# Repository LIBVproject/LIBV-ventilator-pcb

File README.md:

# LIBV Open Source Ventilator

Check out our [www.bvmvent.org](https://www.bvmvent.org/) for updates.

**The Problem:** The COVID-19 Pandemic has highlighted the scarcity of potentially life-saving resources around the world.

**Our Challenge:** Design and Engineer an Open Source, low cost (sub $150) ventilator using readily available materials for rapid deployment in developing countries where there may not be an alternative.

Who we are: A Collective of Engineers, Medics and Scientists from across the world, centred around a hub in Phnom Penh, Cambodia.
Help Us: We need Volunteers, a Community of Contributors and Donors to join us and help us deliver our vision.

## Arduino Program

Check out our [Arduino Program](https://github.com/LIBVproject/LIBV-ventilator).

## Electronics PCB

The LIBV electronics are based on an Arduino Nano (Atmega328) architecture.

### Circuit Digram

### Printed PCB

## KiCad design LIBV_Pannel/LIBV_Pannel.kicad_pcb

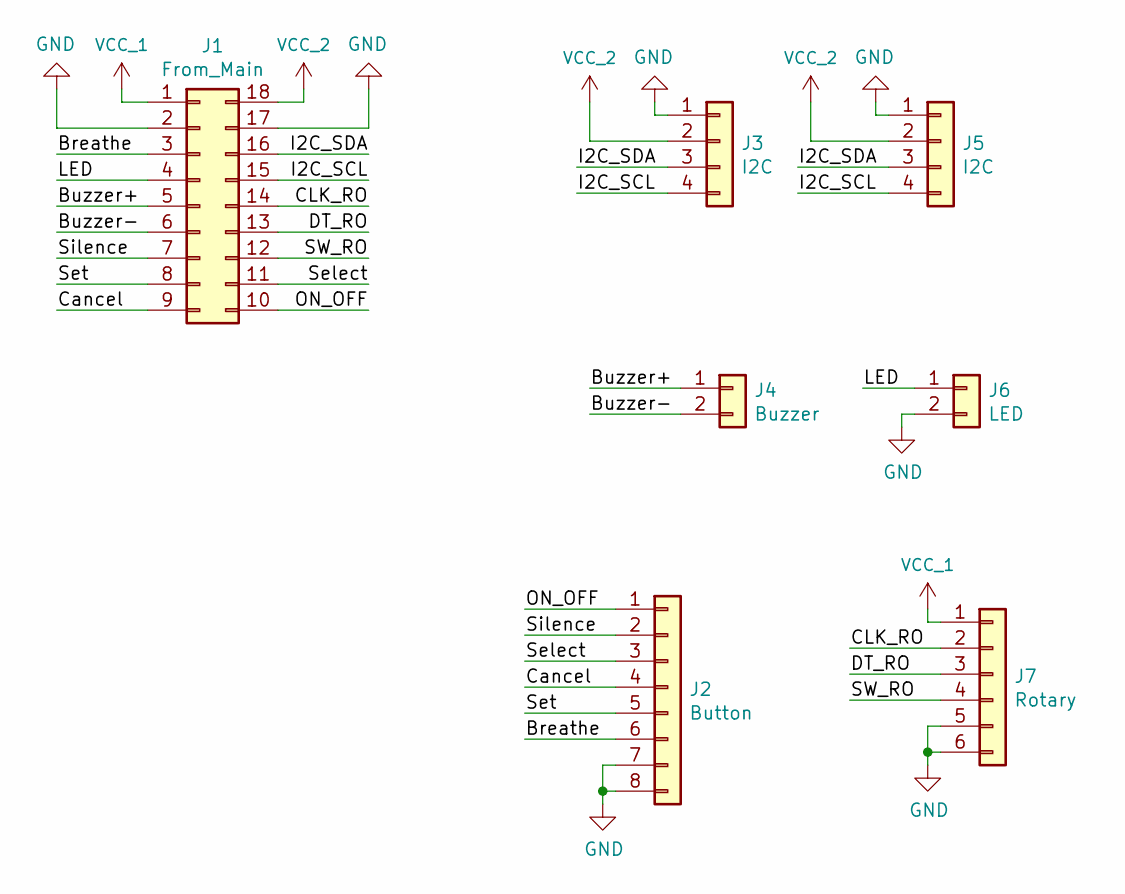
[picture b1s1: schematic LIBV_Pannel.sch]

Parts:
J1: From_Main; PinHeader_2x09_P2.54mm_Vertical
J2: Button; JST_PH_B8B-PH-K_1x08_P2.00mm_Vertical
J3, J5: I2C; JST_PH_B4B-PH-K_1x04_P2.00mm_Vertical
J4: Buzzer; JST_PH_B2B-PH-K_1x02_P2.00mm_Vertical
J6: LED; JST_PH_B2B-PH-K_1x02_P2.00mm_Vertical
J7: Rotary; JST_PH_B6B-PH-K_1x06_P2.00mm_Vertical

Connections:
/Breathe: J1.3, J2.6
/Buzzer+: J1.5, J4.1
/Buzzer-: J1.6, J4.2
/CLK_RO: J1.14, J7.2
/Cancel: J1.9, J2.4
/DT_RO: J1.13, J7.3
/I2C_SCL: J1.15, J3.4, J5.4
/I2C_SDA: J1.16, J3.3, J5.3
/LED: J1.4, J6.1
/ON_OFF: J1.10, J2.1
/SW_RO: J1.12, J7.4
/Select: J1.11, J2.3
/Set: J1.8, J2.5
/Silence: J1.7, J2.2
GND: J1.2, J1.17, J2.7, J2.8, J3.1, J5.1, J6.2, J7.5, J7.6
VCC_1: J1.1, J7.1
VCC_2: J1.18, J3.2, J5.2

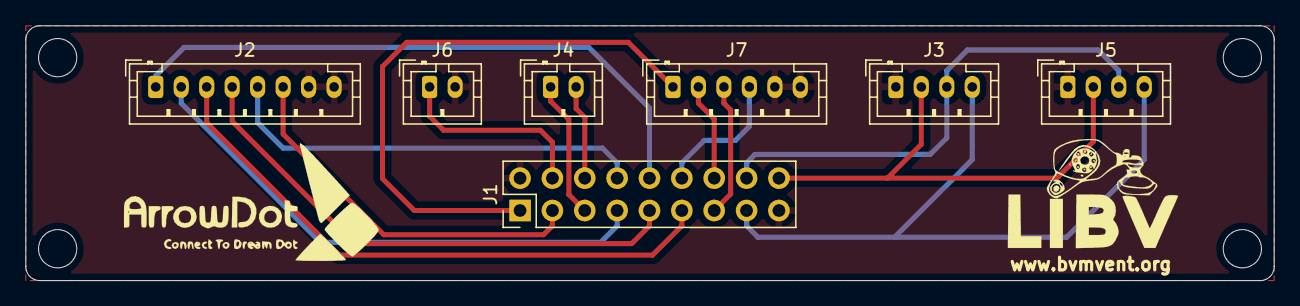
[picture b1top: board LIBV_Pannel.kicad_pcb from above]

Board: 2 copper layers, 98.0 x 20.0 mm, 7 parts (0 on the bottom side), 17 nets.

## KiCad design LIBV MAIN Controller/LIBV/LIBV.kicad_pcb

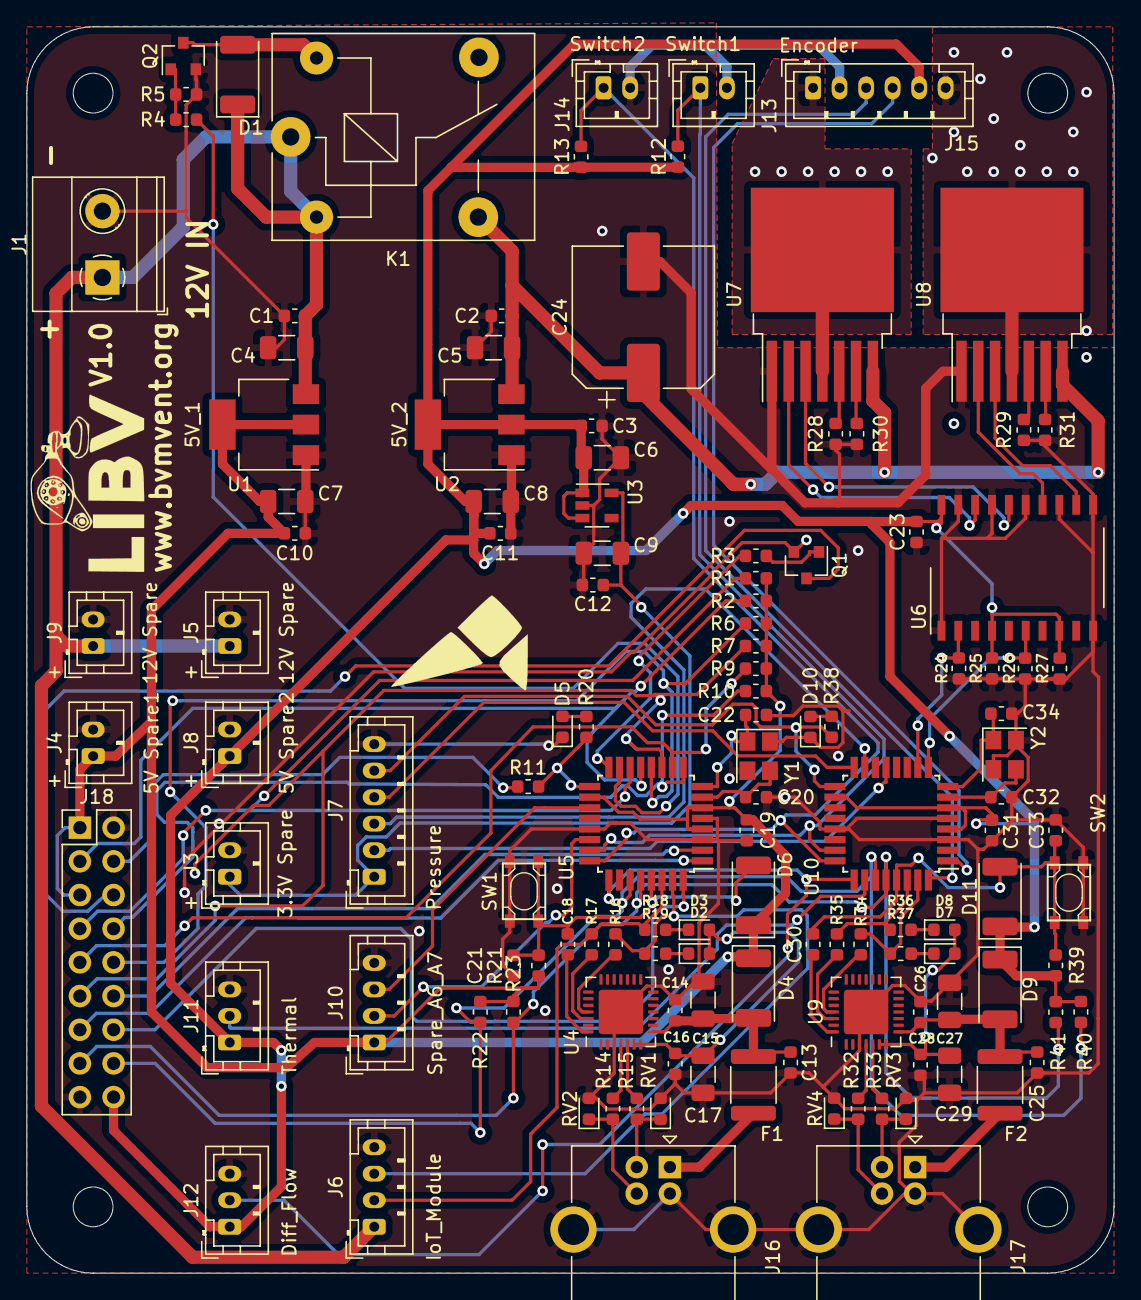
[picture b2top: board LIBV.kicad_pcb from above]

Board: 2 copper layers, 82.0 x 94.0 mm, 125 parts (0 on the bottom side), 85 nets.

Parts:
C1, C2, C3, C10, C11, C12, C13, C14, C16, C18, C19, C25, C26, C28, C30, C31: 100n; C_0603_1608Metric
C4, C5, C6, C7, C8, C9, C15, C17, C27, C29: 10u; C_1206_3216Metric
C20, C21, C22, C32, C33, C34: 22p; C_0603_1608Metric
C23: 100p; C_0603_1608Metric
C24: 470u; CP_Elec_10x10.5
D1, D6, D11: D; D_2010_5025Metric
D2, D7: TX0; LED_0603_1608Metric
D3, D8: RX0; LED_0603_1608Metric
D4, D9: SS34; D_2010_5025Metric
D5, D10: LED; LED_0603_1608Metric
F1, F2: Fuse_USB; Fuse_1812_4532Metric
J1: Power Input; TerminalBlock_Phoenix_MKDS-1,5-2_1x02_P5.00mm_Horizontal
J3: 3.3V Spare; JST_PH_B2B-PH-K_1x02_P2.00mm_Vertical
J4: 5V Spare1; JST_PH_B2B-PH-K_1x02_P2.00mm_Vertical
J5, J9: 12V Spare; JST_PH_B2B-PH-K_1x02_P2.00mm_Vertical
J6: IoT_Module; JST_PH_B4B-PH-K_1x04_P2.00mm_Vertical
J7: Pressure; JST_PH_B6B-PH-K_1x06_P2.00mm_Vertical
J8: 5V Spare2; JST_PH_B2B-PH-K_1x02_P2.00mm_Vertical
J10: Spare_A6_A7; JST_PH_B4B-PH-K_1x04_P2.00mm_Vertical
J11: Thermal; JST_PH_B3B-PH-K_1x03_P2.00mm_Vertical
J12: Diff_Flow; JST_PH_B3B-PH-K_1x03_P2.00mm_Vertical
J13: Switch1; JST_PH_B2B-PH-K_1x02_P2.00mm_Vertical
J14: Switch2; JST_PH_B2B-PH-K_1x02_P2.00mm_Vertical
J15: Encoder; JST_PH_B6B-PH-K_1x06_P2.00mm_Vertical
J16, J17: USB_B; USB_B_OST_USB-B1HSxx_Horizontal
J18: To_Pannel; PinHeader_2x09_P2.54mm_Vertical
K1: SANYOU_SRD_Form_C; Relay_SPDT_SANYOU_SRD_Series_Form_C
Q1, Q2: 1P; SOT-23
R1, R2, R5, R6, R7, R9, R10, R12, R13, R21, R22, R23, R39, R40, R41: 10k; R_0603_1608Metric
R3, R4, R11, R16, R17, R18, R19, R24, R25, R26, R27, R28, R29, R30, R31, R34, R35, R36, R37: 1k; R_0603_1608Metric
R14, R15, R32, R33: 22; R_0603_1608Metric
R20, R38: 470; R_0603_1608Metric
RV1, RV2, RV3, RV4: ESD; D_0603_1608Metric
SW1, SW2: RST; Button_Switch_3.2x4.2
U1, U2: AMS1117-5.0; SOT-223-3_TabPin2
U3: LP2985-3.3; SOT-23-5
U4, U9: CP2102N-A01-GQFN28; QFN-28-1EP_5x5mm_P0.5mm_EP3.35x3.35mm
U5, U10: ATmega328-AU; TQFP-32_7x7mm_P0.8mm
U6: 74HC244; SO-20_12.8x7.5mm_P1.27mm
U7, U8: BTN7970B; TO-263-7_TabPin8
Y1, Y2: 16Mz; Crystal_SMD_3225-4Pin_3.2x2.5mm

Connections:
+3V3: C9.1, C12.1, J3.1, J7.1, U3.5
+12V: C1.1, C4.1, D1.1, J1.1, J5.1, J6.1, J9.1, K1.1, K1.2, U1.3
/ArduinoNano1/+3.3V: C16.1, C17.1, D2.2, D3.2, U4.6, U4.7
/ArduinoNano1/Reset: C18.1, C21.1, D6.2, R21.2, SW1.1, U5.29
/ArduinoNano1/VBUS: C13.1, C14.1, C15.1, D4.2, F1.1, U4.8
/ArduinoNano1/XTAL1: C20.1, U5.7, Y1.3
/ArduinoNano1/XTAL2: C22.1, U5.8, Y1.1
/ArduinoNano2/+3.3V: C28.1, C29.1, D7.2, D8.2, U9.6, U9.7
/ArduinoNano2/RX0: R35.1, R36.1, U10.30
/ArduinoNano2/Reset: C30.1, C33.1, D11.2, R39.2, SW2.1, U10.29
/ArduinoNano2/TX0: R34.1, R37.1, U10.31
/ArduinoNano2/VBUS: C25.1, C26.1, C27.1, D9.2, F2.1, U9.8
/ArduinoNano2/XTAL1: C32.1, U10.7, Y2.3
/ArduinoNano2/XTAL2: C34.1, U10.8, Y2.1
/BTS7960/M+: J15.1, U7.4, U7.8
/BTS7960/M-: J15.6, U8.4, U8.8
/Breathe: J18.3, R2.2, U5.13
/Buzzer: R3.2, U5.16
/Buzzer-: J18.6, Q1.3
/CLK_RO: J18.14, U5.32
/Cancel: J18.9, R9.2, U5.10
/DT_RO: J18.13, U5.1
/Diff_Flow: J12.2, U5.25, U10.25
/I2C_SCL: J18.15, R23.2, R41.2, U5.28, U10.28
/I2C_SDA: J18.16, R22.2, R40.2, U5.27, U10.27
/LED: R11.2, R20.1, U5.17
/L_PWM: R24.2, U6.2, U10.10
/N1_A6: J10.3, U5.19
/N1_A7: J10.2, U5.22
/N1_RX0: J6.2, R17.1, R18.1, U5.30
/N1_TX0: J6.3, R16.1, R19.1, U5.31
/N2_D9: J7.2, U10.13
/N2_D11: J7.3, U10.15
/N2_D12: J7.4, U10.16
/N2_D13: J7.5, R38.1, U10.17
/ON_OFF: J18.10, R6.2, U5.12
/R_PWM: R26.2, U6.6, U10.9
/Relay_Pin: R4.2, U5.15
/SW_RO: J18.12, U5.2
/Select: J18.11, R7.2, U5.11
/Set: J18.8, R10.2, U5.9
/Silence: J18.7, R1.2, U5.14
/Switch1: J13.1, R12.2, U5.23, U10.23
/Switch2: J14.1, R13.2, U5.24, U10.24
/Thermal: J11.2, U10.26
/V_Motor: C2.1, C5.1, C24.1, K1.3, U2.3, U7.7, U8.7
/chA: J15.3, U10.32
/chB: J15.4, U10.1
GND: C1.2, C2.2, C3.2, C4.2, C5.2, C6.2, C7.2, C8.2, C9.2, C10.2, C11.2, C12.2, C13.2, C14.2, C15.2, C16.2, C17.2, C19.2, C20.2, C21.2, C22.2, C23.1, C24.2, C25.2, C26.2, C27.2, C28.2, C29.2, C31.2, C32.2, C33.2, C34.2, D5.1, D10.1, J1.2, J3.2, J4.2, J5.2, J6.4, J7.6, J8.2, J9.2, J10.4, J11.3, J12.3, J13.2, J14.2, J15.2, J16.4, J16.5, J17.4, J17.5, J18.2, J18.17, Q1.2, Q2.2, R5.2, R24.1, R25.1, R26.1, R27.1, R28.1, R29.1, R30.1, R31.1, RV1.2, RV2.2, RV3.2, RV4.2, SW1.2, SW2.2, U1.1, U2.1, U3.2, U4.3, U4.29, U5.3, U5.5, U5.21, U6.1, U6.10, U6.11, U6.13, U6.15, U6.17, U6.19, U7.1, U8.1, U9.3, U9.29, U10.3, U10.5, U10.21, Y1.2, Y1.4, Y2.2, Y2.4
unnamed: C18.2, U4.28
unnamed: C30.2, U9.28
unnamed: D1.2, K1.5, Q2.3
unnamed: D2.1, R19.2
unnamed: D3.1, R18.2
unnamed: D5.2, R20.2
unnamed: D7.1, R37.2
unnamed: D8.1, R36.2
unnamed: D10.2, R38.2
unnamed: F1.2, J16.1
unnamed: F2.2, J17.1
unnamed: J16.2, R15.2, RV1.1
unnamed: J16.3, R14.2, RV2.1
unnamed: J17.2, R33.2, RV3.1
unnamed: J17.3, R32.2, RV4.1
unnamed: J18.4, R11.1
unnamed: Q1.1, R3.1
unnamed: Q2.1, R4.1, R5.1
unnamed: R14.1, U4.4
unnamed: R15.1, U4.5
unnamed: R16.2, U4.25
unnamed: R17.2, U4.26
unnamed: R28.2, U7.5
unnamed: R29.2, U8.5
unnamed: R30.2, U7.6
unnamed: R31.2, U8.6
unnamed: R32.1, U9.4
unnamed: R33.1, U9.5
unnamed: R34.2, U9.25
unnamed: R35.2, U9.26
unnamed: U6.12, U8.3
unnamed: U6.14, U8.2
unnamed: U6.16, U7.3
unnamed: U6.18, U7.2
VCC_1: C7.1, C10.1, C19.1, D4.1, D6.1, J4.1, J10.1, J18.1, J18.5, R1.1, R2.1, R6.1, R7.1, R9.1, R10.1, R21.1, R22.1, R23.1, U1.2, U5.4, U5.6, U5.18
VCC_2: C3.1, C6.1, C8.1, C11.1, C23.2, C31.1, D9.1, D11.1, J8.1, J11.1, J12.1, J15.5, J18.18, R12.1, R13.1, R25.2, R27.2, R39.1, R40.1, R41.1, U2.2, U3.1, U3.3, U6.4, U6.8, U6.20, U10.4, U10.6, U10.18

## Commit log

2020-08-13 V1.0
